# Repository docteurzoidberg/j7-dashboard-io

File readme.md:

# **WIP**

## 3d render

## case

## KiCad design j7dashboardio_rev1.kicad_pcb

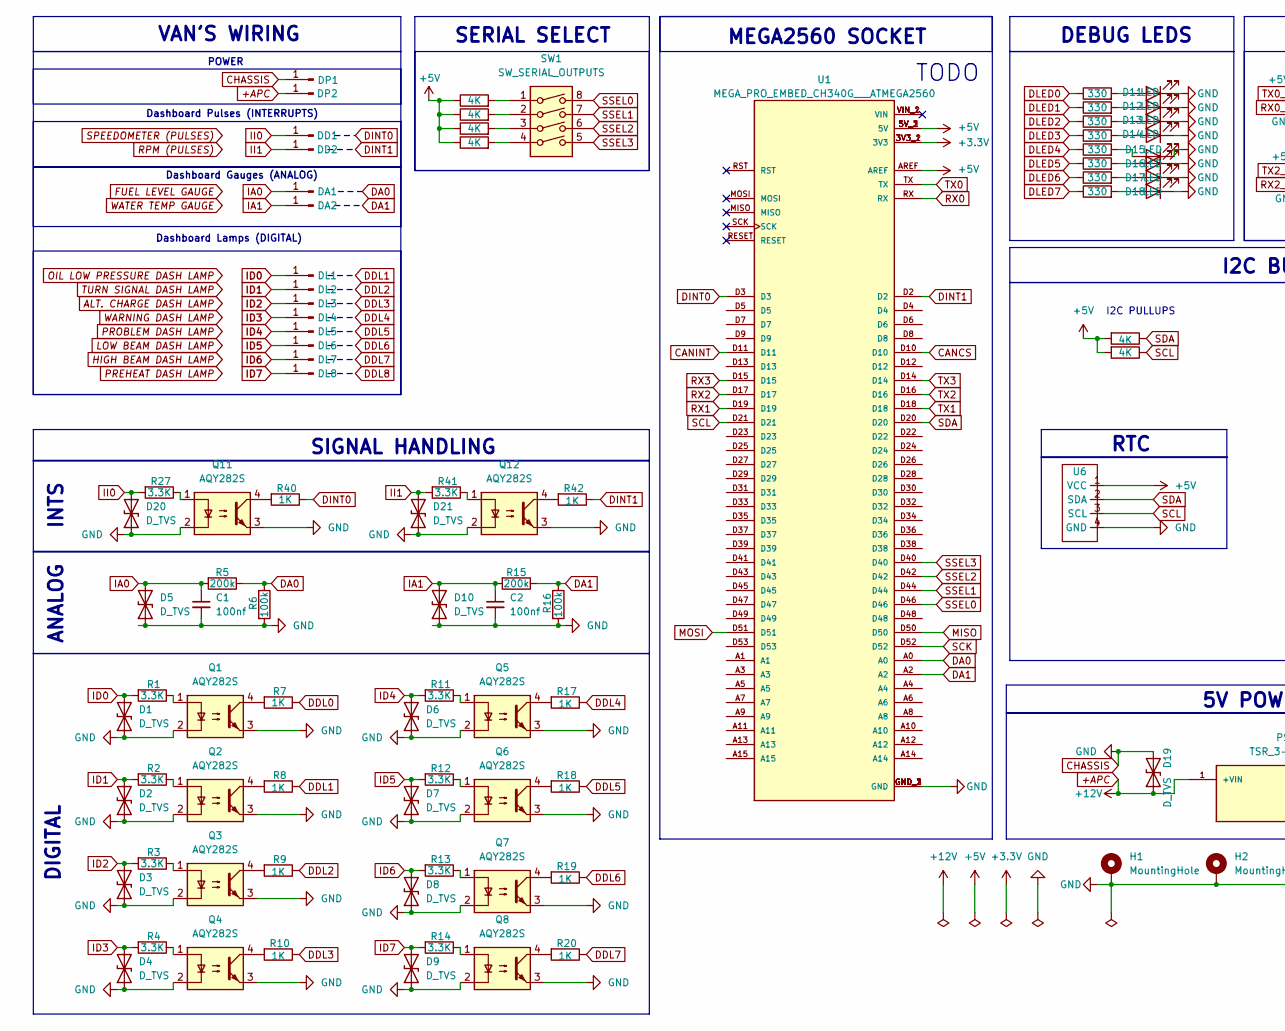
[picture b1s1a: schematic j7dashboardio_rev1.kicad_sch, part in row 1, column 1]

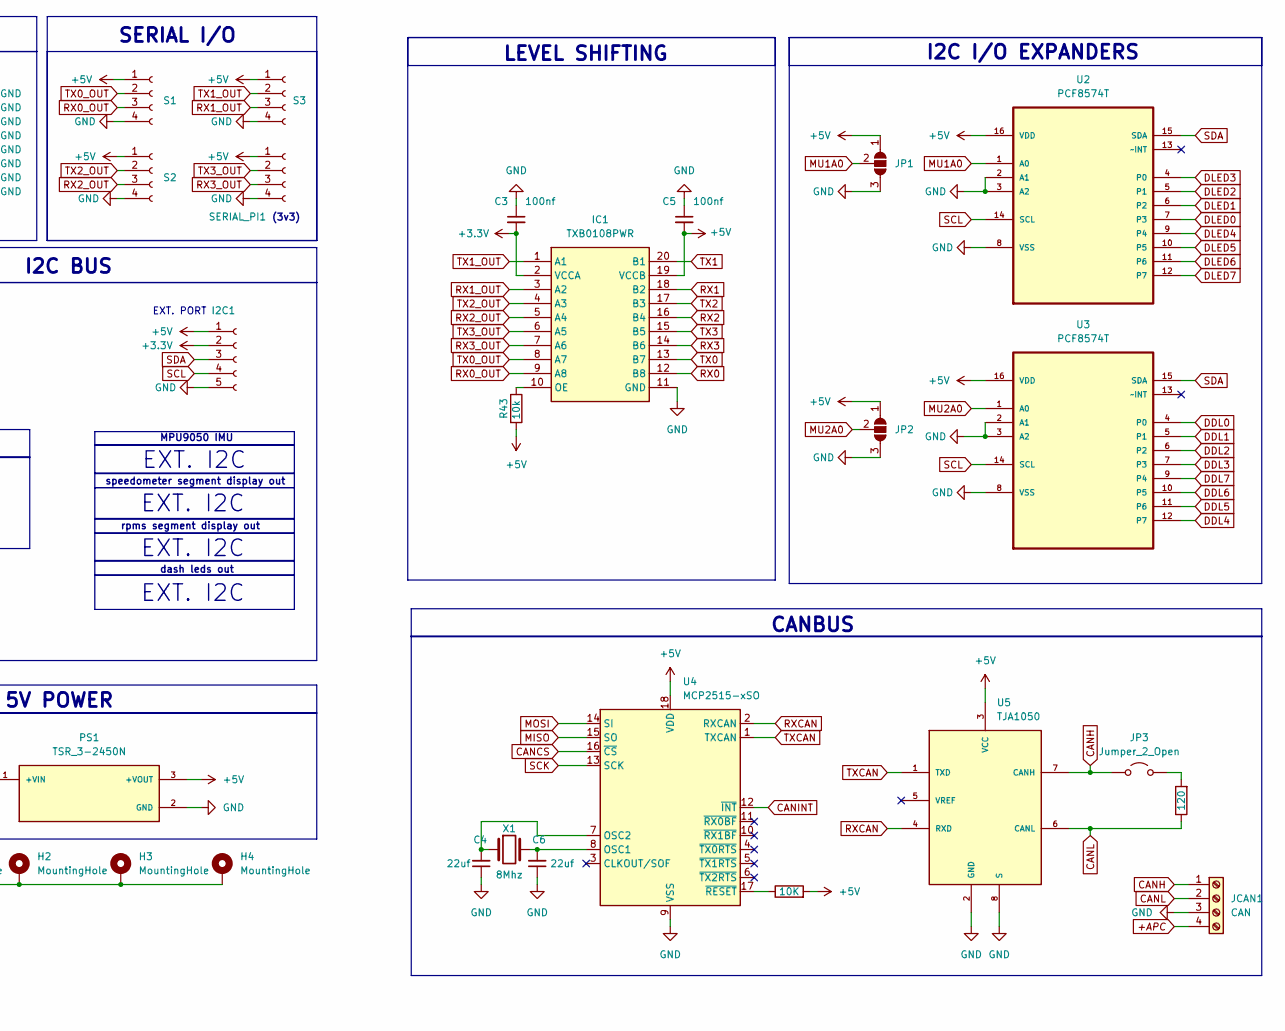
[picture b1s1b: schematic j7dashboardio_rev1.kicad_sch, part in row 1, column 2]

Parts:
C1, C2: 100nf; C_Disc_D3.0mm_W1.6mm_P2.50mm
C3, C5: 100nf; C_0805_2012Metric_Pad1.18x1.45mm_HandSolder
C4, C6: 22uf; C_0805_2012Metric_Pad1.18x1.45mm_HandSolder
D1, D2, D3, D4, D5, D6, D7, D8, D9, D10, D19, D20, D21: D_TVS; DIOM4336X265N
D11, D12, D13, D14, D15, D16, D17, D18: LED; LED_0805_2012Metric_Pad1.15x1.40mm_HandSolder
DA1, DA2: Conn_01x01_Pin; TE_928814-1
DD1, DD2: Conn_01x01_Pin; TE_928814-1
DL1, DL2, DL3, DL4, DL5, DL6, DL7, DL8: Conn_01x01_Pin; TE_928814-1
DP1, DP2: Conn_01x01_Pin; TE_928814-1
H1, H2, H3, H4: MountingHole; MountingHole_3.2mm_M3_Pad_Via
I2C1: Conn_01x05_Socket; JST_XH_S5B-XH-A_1x05_P2.50mm_Horizontal
IC1: TXB0108PWR; SOP65P640X120-20N; Mouser Part Number 595-TXB0108PWR
JCAN1: CAN; TerminalBlock_Phoenix_MKDS-1,5-4-5.08_1x04_P5.08mm_Horizont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
JP1, JP2: SolderJumper_3_Open; SolderJumper-3_P1.3mm_Open_RoundedPad1.0x1.5mm
JP3: Jumper_2_Open; PinHeader_1x02_P2.54mm_Vertical
PS1: TSR_3-2450N; CONV_TSR_3-2450N; PARTREV December 18, 2024; DigiKey_Part_Number 1951-TSR3-2450N-ND
Q1, Q2, Q3, Q4, Q5, Q6, Q7, Q8, Q11, Q12: AQY282S; AQY282SX
R1, R2, R3, R4, R11, R12, R13, R14, R27, R41: 3.3K; R_0805_2012Metric_Pad1.20x1.40mm_HandSolder
R5, R15: 200k; R_0805_2012Metric_Pad1.20x1.40mm_HandSolder
R6, R16: 100k; R_0805_2012Metric_Pad1.20x1.40mm_HandSolder
R7, R8, R9, R10, R17, R18, R19, R20, R40, R42: 1K; R_0805_2012Metric_Pad1.20x1.40mm_HandSolder
R21: 10K; R_0805_2012Metric_Pad1.20x1.40mm_HandSolder
R22: 120; R_0805_2012Metric_Pad1.20x1.40mm_HandSolder
R25, R26, R36, R37, R38, R39: 4K; R_0805_2012Metric_Pad1.20x1.40mm_HandSolder
R28, R29, R30, R31, R32, R33, R34, R35: 330; R_0805_2012Metric_Pad1.20x1.40mm_HandSolder
R43: 10k; R_0805_2012Metric_Pad1.20x1.40mm_HandSolder
S1, S2, S3: Conn_01x04_Socket; JST_XH_S4B-XH-A_1x04_P2.50mm_Horizontal
SERIAL_PI1: Conn_01x04_Socket; JST_XH_S4B-XH-A_1x04_P2.50mm_Horizontal
SW1: SW_SERIAL_OUTPUTS; SW_DIP_SPSTx04_Slide_9.78x12.34mm_W8.61mm_P2.54mm
U1: MEGA_PRO_EMBED_CH340G___ATMEGA2560; MODULE_MEGA_PRO_EMBED_CH340G___ATMEGA2560; PARTREV 12/May/2017
U2, U3: PCF8574T; PCF8574T_SOIC16; MPN PCF8574T
U4: MCP2515-xSO; SOIC-18W_7.5x11.6mm_P1.27mm
U5: TJA1050; TJA1050_SOP8
U6: DS3231_RTC_MODULE
X1: 8Mhz; Crystal_SMD_3225-4Pin_3.2x2.5mm_HandSoldering

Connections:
+3.3V: C3.2, I2C1.2, IC1.2 (VCCA), U1.3V3_1 (3V3), U1.3V3_2 (3V3)
+5V: C5.2, I2C1.1, IC1.19 (VCCB), JP1.1 (A), JP2.1 (A), PS1.3 (+VOUT), R21.2, R25.2, R26.2, R36.1, R37.1, R38.1, R39.1, R43.2, S1.1, S2.1, S3.1, SERIAL_PI1.1, U1.5V_1 (5V), U1.5V_2 (5V), U1.5V_3 (5V), U1.AREF, U2.16 (VDD), U3.16 (VDD), U4.18 (VDD), U5.3 (VCC), U6.1 (VCC)
+APC: D19.1 (A1), DP2.1, JCAN1.4, PS1.1 (+VIN)
CANCS: U1.D10, U4.16 (~CS)
CANH: JCAN1.1, JP3.1 (A), U5.7 (CANH)
CANINT: U1.D11, U4.12 (~INT)
CANL: JCAN1.2, R22.1, U5.6 (CANL)
CHASSIS: C1.2, C2.2, C3.1, C4.1, C5.1, C6.1, D1.1 (A1), D2.1 (A1), D3.1 (A1), D4.1 (A1), D5.1 (A1), D6.1 (A1), D7.1 (A1), D8.1 (A1), D9.1 (A1), D10.1 (A1), D11.1 (K), D12.1 (K), D13.1 (K), D14.1 (K), D15.1 (K), D16.1 (K), D17.1 (K), D18.1 (K), D19.2 (A2), D20.1 (A1), D21.1 (A1), DP1.1, H1.1, H2.1, H3.1, H4.1, I2C1.5, IC1.11 (GND), JCAN1.3, JP1.3 (B), JP2.3 (B), PS1.2 (GND), Q1.2, Q1.3, Q2.2, Q2.3, Q3.2, Q3.3, Q4.2, Q4.3, Q5.2, Q5.3, Q6.2, Q6.3, Q7.2, Q7.3, Q8.2, Q8.3, Q11.2, Q11.3, Q12.2, Q12.3, R6.2, R16.2, S1.4, S2.4, S3.4, SERIAL_PI1.4, U1.GND_1 (GND), U1.GND_2 (GND), U1.GND_3 (GND), U2.2 (A1), U2.3 (A2), U2.8 (VSS), U3.2 (A1), U3.3 (A2), U3.8 (VSS), U4.9 (VSS), U5.2 (GND), U5.8 (S), U6.4 (GND)
DA0: R5.1, R6.1, U1.A0
DA1: R15.1, R16.1, U1.A2
DDL0: R7.1, U3.4 (P0)
DDL1: R8.1, U3.5 (P1)
DDL2: R9.1, U3.6 (P2)
DDL3: R10.1, U3.7 (P3)
DDL4: R17.1, U3.12 (P7)
DDL5: R18.1, U3.11 (P6)
DDL6: R19.1, U3.10 (P5)
DDL7: R20.1, U3.9 (P4)
DINT0: R40.1, U1.D3
DINT1: R42.1, U1.D2
DLED0: R28.1, U2.7 (P3)
DLED1: R29.1, U2.6 (P2)
DLED2: R30.1, U2.5 (P1)
DLED3: R31.1, U2.4 (P0)
DLED4: R32.1, U2.9 (P4)
DLED5: R33.1, U2.10 (P5)
DLED6: R34.1, U2.11 (P6)
DLED7: R35.1, U2.12 (P7)
IA0: C1.1, D5.2 (A2), DA1.1, R5.2
IA1: C2.1, D10.2 (A2), DA2.1, R15.2
ID0: D1.2 (A2), DL1.1, R1.2
ID1: D2.2 (A2), DL2.1, R2.2
ID2: D3.2 (A2), DL3.1, R3.2
ID3: D4.2 (A2), DL4.1, R4.2
ID4: D6.2 (A2), DL5.1, R11.2
ID5: D7.2 (A2), DL6.1, R12.2
ID6: D8.2 (A2), DL7.1, R13.2
ID7: D9.2 (A2), DL8.1, R14.2
II0: D20.2 (A2), DD1.1, R27.2
II1: D21.2 (A2), DD2.1, R41.2
MISO: U1.D50, U4.15 (SO)
MOSI: U1.D51, U4.14 (SI)
MU1A0: JP1.2 (C), U2.1 (A0)
MU2A0: JP2.2 (C), U3.1 (A0)
unnamed: D11.2 (A), R28.2
unnamed: D12.2 (A), R29.2
unnamed: D13.2 (A), R30.2
unnamed: D14.2 (A), R31.2
unnamed: D15.2 (A), R32.2
unnamed: D16.2 (A), R33.2
unnamed: D17.2 (A), R34.2
unnamed: D18.2 (A), R35.2
unnamed: IC1.10 (OE), R43.1
unnamed: JP3.2 (B), R22.2
unnamed: Q1.1, R1.1
unnamed: Q1.4, R7.2
unnamed: Q2.1, R2.1
unnamed: Q2.4, R8.2
unnamed: Q3.1, R3.1
unnamed: Q3.4, R9.2
unnamed: Q4.1, R4.1
unnamed: Q4.4, R10.2
unnamed: Q5.1, R11.1
unnamed: Q5.4, R17.2
unnamed: Q6.1, R12.1
unnamed: Q6.4, R18.2
unnamed: Q7.1, R13.1
unnamed: Q7.4, R19.2
unnamed: Q8.1, R14.1
unnamed: Q8.4, R20.2
unnamed: Q11.1, R27.1
unnamed: Q11.4, R40.2
unnamed: Q12.1, R41.1
unnamed: Q12.4, R42.2
unnamed: R36.2, SW1.1
unnamed: R37.2, SW1.2
unnamed: R38.2, SW1.3
unnamed: R39.2, SW1.4
unnamed: C6.2, U4.8 (OSC1), X1.2
unnamed: C4.2, U4.7 (OSC2), X1.1
unnamed: R21.1, U4.17 (~RESET)
RX0: IC1.12 (B8), U1.RX
RX0_OUT: IC1.9 (A8), S1.3
RX1: IC1.18 (B2), U1.D19
RX1_OUT: IC1.3 (A2), S3.3
RX2: IC1.16 (B4), U1.D17
RX2_OUT: IC1.5 (A4), S2.3
RX3: IC1.14 (B6), U1.D15
RX3_OUT: IC1.7 (A6), SERIAL_PI1.3
RXCAN: U4.2 (RXCAN), U5.4 (RXD)
SCK: U1.D52, U4.13 (SCK)
SCL: I2C1.4, R26.1, U1.D21, U2.14 (SCL), U3.14 (SCL), U6.3 (SCL)
SDA: I2C1.3, R25.1, U1.D20, U2.15 (SDA), U3.15 (SDA), U6.2 (SDA)
SSEL0: SW1.8, U1.D46
SSEL1: SW1.7, U1.D44
SSEL2: SW1.6, U1.D42
SSEL3: SW1.5, U1.D40
TX0: IC1.13 (B7), U1.TX
TX0_OUT: IC1.8 (A7), S1.2
TX1: IC1.20 (B1), U1.D18
TX1_OUT: IC1.1 (A1), S3.2
TX2: IC1.17 (B3), U1.D16
TX2_OUT: IC1.4 (A3), S2.2
TX3: IC1.15 (B5), U1.D14
TX3_OUT: IC1.6 (A5), SERIAL_PI1.2
TXCAN: U4.1 (TXCAN), U5.1 (TXD)

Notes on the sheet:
speedometer segment display out
dash leds out
I2C BUS
LEVEL SHIFTING
5V POWER
RTC
POWER
SIGNAL HANDLING
Dashboard Pulses (INTERRUPTS)
Dashboard Gauges (ANALOG)
EXT. I2C
rpms segment display out
VAN'S WIRING
I2C I/O EXPANDERS
MPU9050 IMU
DEBUG LEDS
(3v3)
CANBUS
Dashboard Lamps (DIGITAL)
INTS
EXT. PORT
TODO
DIGITAL
ANALOG
SERIAL I/O
SERIAL SELECT
I2C PULLUPS
MEGA2560 SOCKET

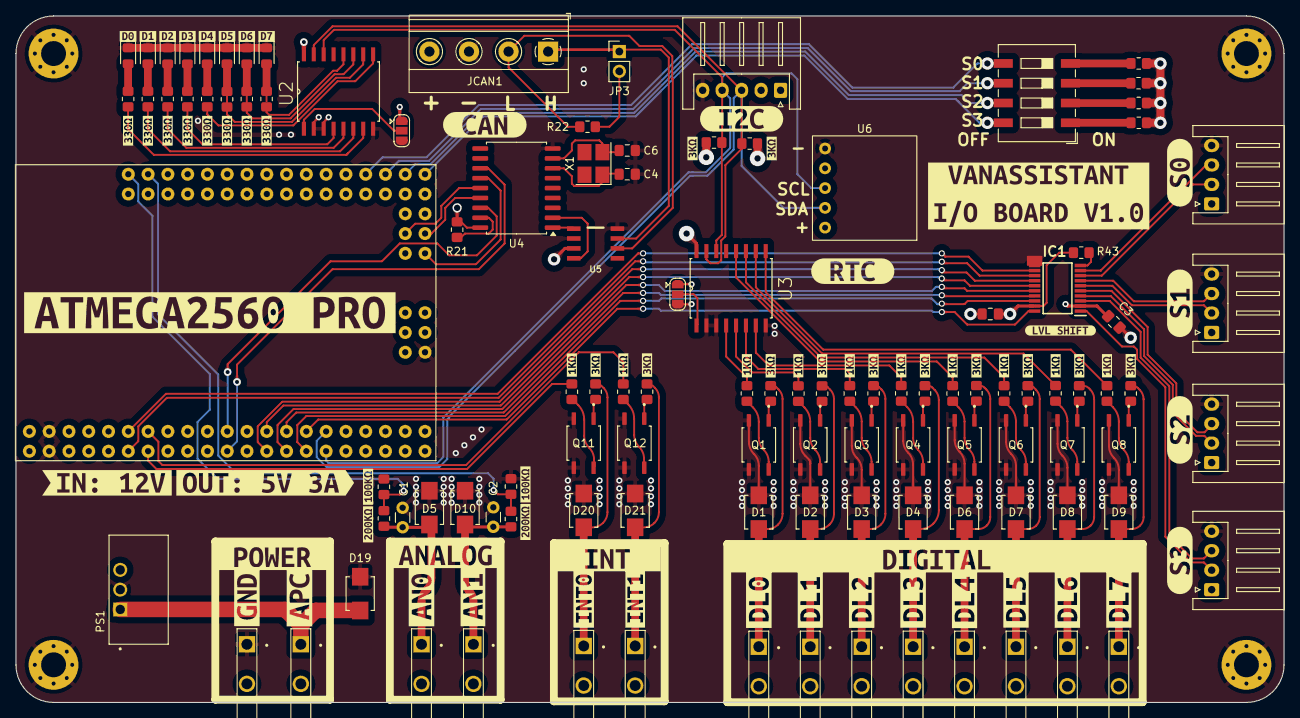
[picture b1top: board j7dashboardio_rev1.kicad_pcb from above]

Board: 4 copper layers, 162.8 x 88.1 mm, 187 parts (0 on the bottom side), 106 nets.

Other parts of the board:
kibuzzard-10: G***; kibuzzard-66BDFE2F
kibuzzard-12: G***; kibuzzard-66BDFFE7
kibuzzard-13: G***; kibuzzard-66BDFCC3
kibuzzard-14: G***; kibuzzard-66BDFCD7
kibuzzard-15: G***; kibuzzard-66C26DEF
kibuzzard-16: G***; kibuzzard-66C27559
kibuzzard-17: G***; kibuzzard-66C26DD9
kibuzzard-18: G***; kibuzzard-66BE5FFD
kibuzzard-19: G***; kibuzzard-66C26DE5
kibuzzard-20: G***; kibuzzard-66C26DF6
kibuzzard-21: G***; kibuzzard-66C26E39
kibuzzard-23: G***; kibuzzard-66C26E7C
kibuzzard-24: G***; kibuzzard-66C26E45
kibuzzard-25: G***; kibuzzard-66C26E3E
kibuzzard-26: G***; kibuzzard-66C27575
kibuzzard-27: G***; kibuzzard-66C26E51
kibuzzard-28: G***; kibuzzard-66C26E56
kibuzzard-29: G***; kibuzzard-66C26E65
kibuzzard-30: G***; kibuzzard-66C26E6B
kibuzzard-31: G***; kibuzzard-66C26E5F
kibuzzard-32: G***; kibuzzard-66BDFCE8
kibuzzard-66C28E17: G***; kibuzzard-66C28E17
kibuzzard-66C282E1, kibuzzard-66C282E1#2, kibuzzard-66C282E1#3, kibuzzard-66C282E1#4, kibuzzard-66C282E1#5, kibuzzard-66C282E1#6, kibuzzard-66C282E1#7, kibuzzard-66C282E1#8, kibuzzard-66C282E1#9, kibuzzard-66C282E1#10: G***; kibuzzard-66C282E1
kibuzzard-66C282ED, kibuzzard-66C282ED#2, kibuzzard-66C282ED#3, kibuzzard-66C282ED#4, kibuzzard-66C282ED#5, kibuzzard-66C282ED#6, kibuzzard-66C282ED#7, kibuzzard-66C282ED#8, kibuzzard-66C282ED#9, kibuzzard-66C282ED#10, kibuzzard-66C282ED#11, kibuzzard-66C282ED#12: G***; kibuzzard-66C282ED
kibuzzard-66C3314C: G***; kibuzzard-66C3314C
kibuzzard-66C3315C: G***; kibuzzard-66C3315C
kibuzzard-66C3316F: G***; kibuzzard-66C3316F
kibuzzard-66C33147: G***; kibuzzard-66C33147
kibuzzard-66C33151: G***; kibuzzard-66C33151
kibuzzard-66C33156: G***; kibuzzard-66C33156
kibuzzard-66C33164: G***; kibuzzard-66C33164
kibuzzard-66C33169: G***; kibuzzard-66C33169
kibuzzard-66E37C83: G***; kibuzzard-66E37C83
kibuzzard-66E37CCF: G***; kibuzzard-66E37CCF
kibuzzard-66E3800B: G***; kibuzzard-66E3800B
kibuzzard-66E21539, kibuzzard-66E21539#2, kibuzzard-66E21539#3, kibuzzard-66E21539#4, kibuzzard-66E21539#5, kibuzzard-66E21539#6, kibuzzard-66E21539#7, kibuzzard-66E21539#8: G***; kibuzzard-66E21539
kibuzzard-66E38004: G***; kibuzzard-66E38004
kibuzzard-66E38165, kibuzzard-66E38165#2: G***; kibuzzard-66E38165
kibuzzard-66E38172, kibuzzard-66E38172#2: G***; kibuzzard-66E38172
kibuzzard-67B619C3: G***; kibuzzard-67B619C3
kibuzzard-67B666F5: G***; kibuzzard-67B666F5
kibuzzard-68631072: G***; kibuzzard-68631072
kibuzzard-68631628: G***; kibuzzard-68631628

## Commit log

2025-07-10 readme
2025-07-10 readme add case
